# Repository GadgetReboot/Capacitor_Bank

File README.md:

# Capacitor_Bank
<br><br><BR><BR>
Capacitor substitution box  1nF to 10 uF

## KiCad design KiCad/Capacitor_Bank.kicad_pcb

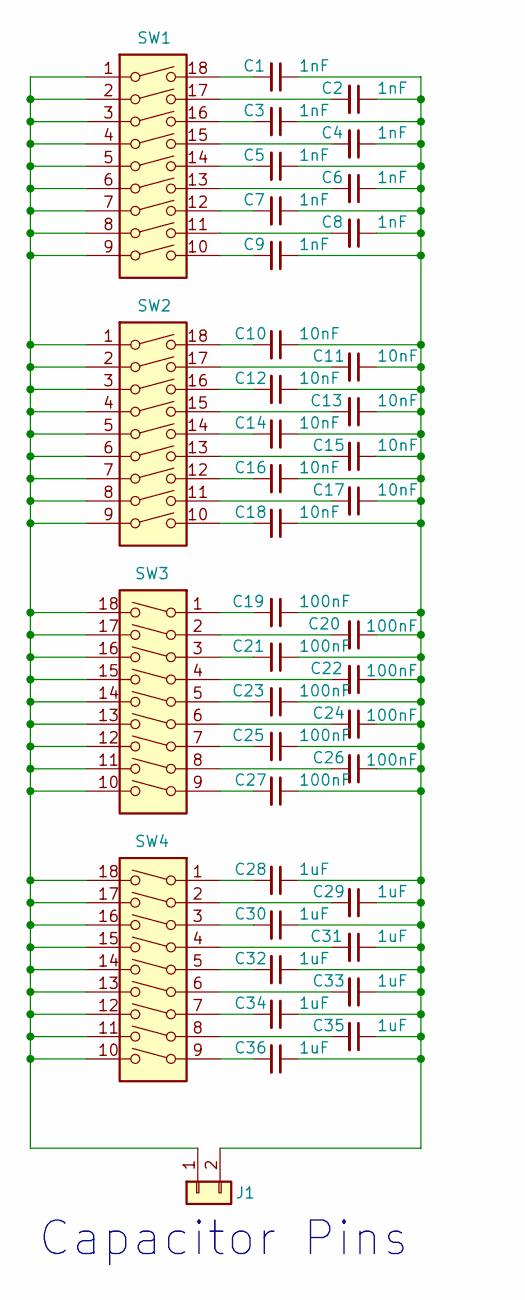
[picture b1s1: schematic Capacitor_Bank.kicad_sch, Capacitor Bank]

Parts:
C1, C2, C3, C4, C5, C6, C7, C8, C9: 1nF; C_Disc_D4.7mm_W2.5mm_P5.00mm
C10, C11, C12, C13, C14, C15, C16, C17, C18: 10nF; C_Disc_D4.7mm_W2.5mm_P5.00mm
C19, C20, C21, C22, C23, C24, C25, C26, C27: 100nF; C_Disc_D10.5mm_W5.0mm_P7.50mm
C28, C29, C30, C31, C32, C33, C34, C35, C36: 1uF; C_Rect_L16.5mm_W5.0mm_P15.00mm_MKT
J1: Conn_01x02; PinHeader_1x02_P2.54mm_Vertical
SW1, SW2, SW3, SW4: SW_DIP_x09; SW_DIP_SPSTx09_Slide_9.78x25.04mm_W7.62mm_P2.54mm

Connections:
unnamed: C1.2, SW1.18
unnamed: C2.2, SW1.17
unnamed: C3.2, SW1.16
unnamed: C4.2, SW1.15
unnamed: C5.2, SW1.14
unnamed: C6.2, SW1.13
unnamed: C7.2, SW1.12
unnamed: C8.2, SW1.11
unnamed: C9.2, SW1.10
unnamed: C10.2, SW2.18
unnamed: C11.2, SW2.17
unnamed: C12.2, SW2.16
unnamed: C13.2, SW2.15
unnamed: C14.2, SW2.14
unnamed: C15.2, SW2.13
unnamed: C16.2, SW2.12
unnamed: C17.2, SW2.11
unnamed: C18.2, SW2.10
unnamed: C19.2, SW3.1
unnamed: C20.2, SW3.2
unnamed: C21.2, SW3.3
unnamed: C22.2, SW3.4
unnamed: C23.2, SW3.5
unnamed: C24.2, SW3.6
unnamed: C25.2, SW3.7
unnamed: C26.2, SW3.8
unnamed: C27.2, SW3.9
unnamed: C28.2, SW4.1
unnamed: C29.2, SW4.2
unnamed: C30.2, SW4.3
unnamed: C31.2, SW4.4
unnamed: C32.2, SW4.5
unnamed: C33.2, SW4.6
unnamed: C34.2, SW4.7
unnamed: C35.2, SW4.8
unnamed: C36.2, SW4.9
unnamed: J1.1, SW1.1, SW1.2, SW1.3, SW1.4, SW1.5, SW1.6, SW1.7, SW1.8, SW1.9, SW2.1, SW2.2, SW2.3, SW2.4, SW2.5, SW2.6, SW2.7, SW2.8, SW2.9, SW3.10, SW3.11, SW3.12, SW3.13, SW3.14, SW3.15, SW3.16, SW3.17, SW3.18, SW4.10, SW4.11, SW4.12, SW4.13, SW4.14, SW4.15, SW4.16, SW4.17, SW4.18
unnamed: C1.1, C2.1, C3.1, C4.1, C5.1, C6.1, C7.1, C8.1, C9.1, C10.1, C11.1, C12.1, C13.1, C14.1, C15.1, C16.1, C17.1, C18.1, C19.1, C20.1, C21.1, C22.1, C23.1, C24.1, C25.1, C26.1, C27.1, C28.1, C29.1, C30.1, C31.1, C32.1, C33.1, C34.1, C35.1, C36.1, J1.2

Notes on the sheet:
Capacitor Pins

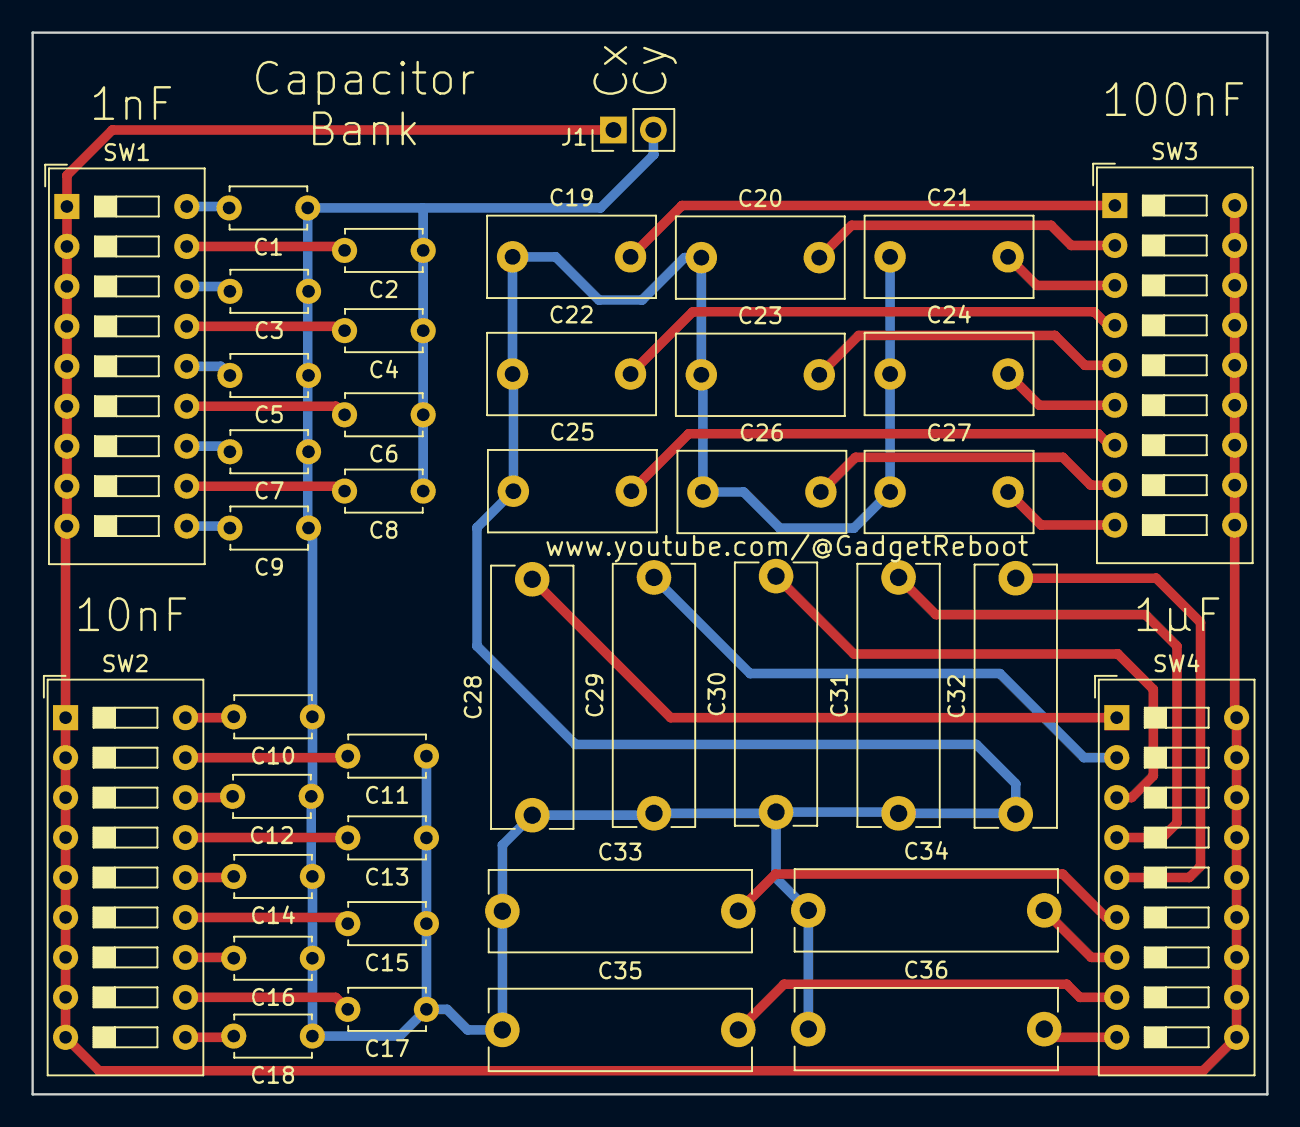
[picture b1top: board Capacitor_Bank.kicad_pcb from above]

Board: 2 copper layers, 78.5 x 67.5 mm, 41 parts (0 on the bottom side), 38 nets.
